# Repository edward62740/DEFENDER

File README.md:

# DEFENDER

This is a 2.4GHz Wi-Fi scanner for estimating channel usage and detect deauthentication attacks. The collected data is sent to a database to be analyzed and provide notifications.

## Design Objectives

* Provide notifications on deauthentication attacks (including which channel(s) they are on).
* Allow for measurement of 2.4GHz Wi-Fi channel packets per second to estimate channel noise. Since Wi-Fi is the biggest "polluter" of 2.4GHz in residential environments, this data can be used to steer other linked systems clear of noisy channel frequencies.

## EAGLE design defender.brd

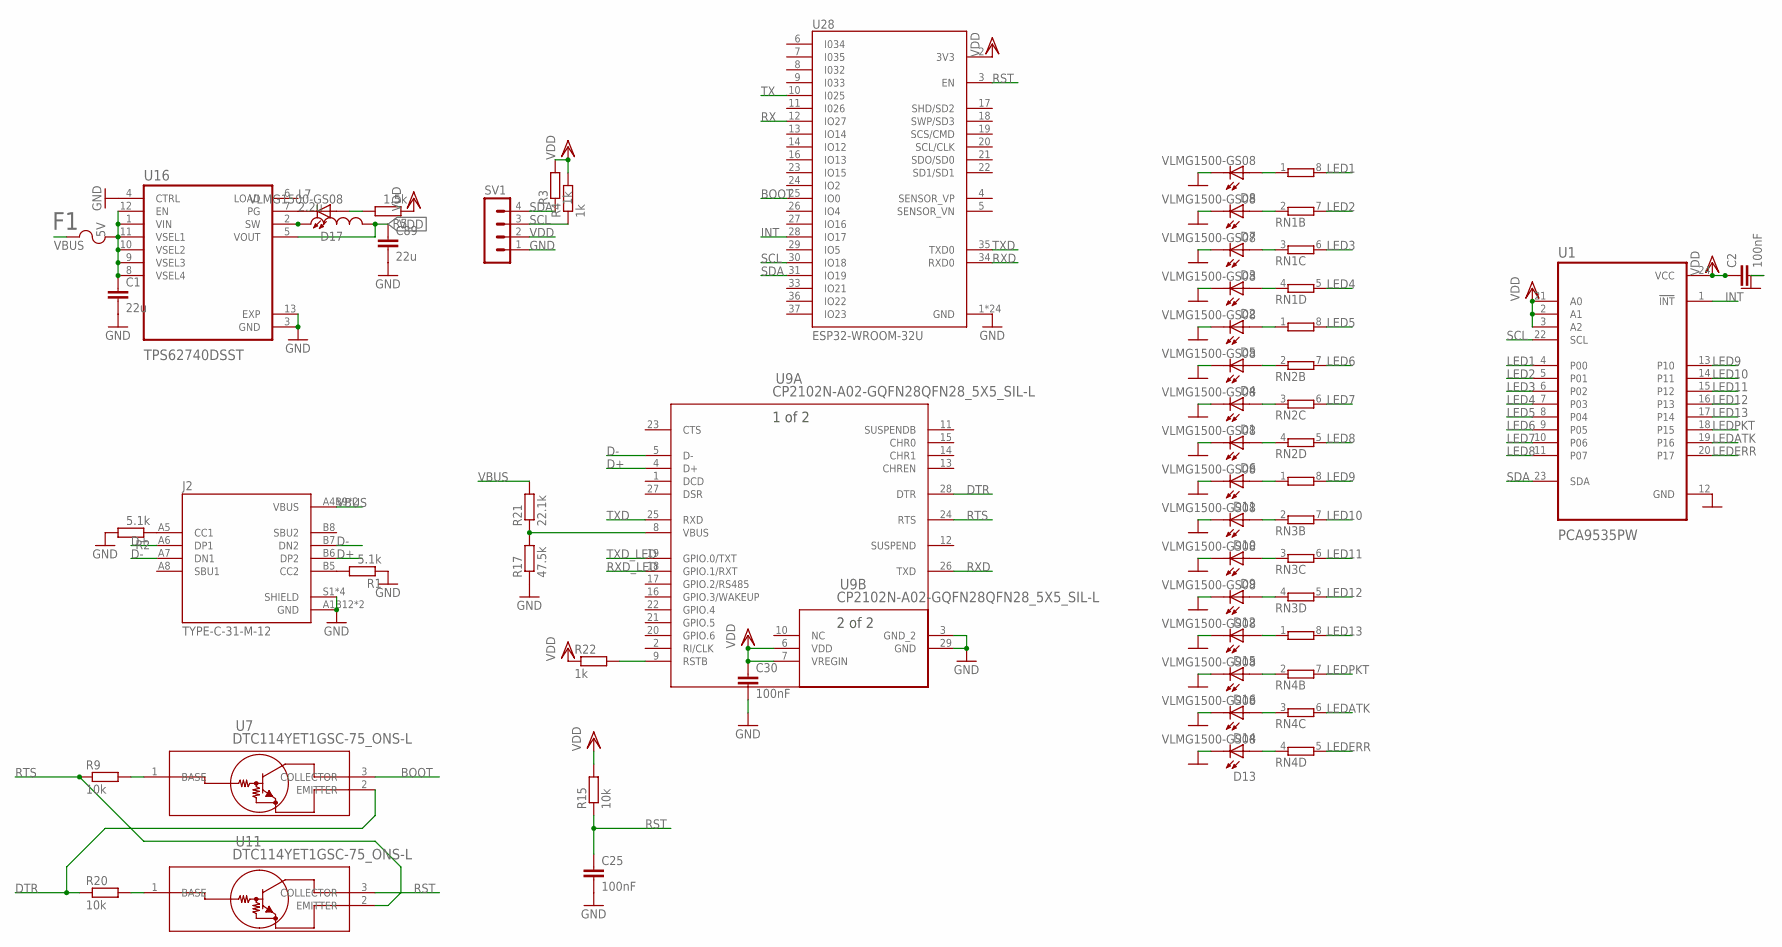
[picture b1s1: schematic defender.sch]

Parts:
C1, C89: 22u; C0603R
C2, C25, C30: 100nF; C0402
D1, D2, D3, D4, D5, D6, D7, D8, D9, D10, D11, D12, D13, D14, D15, D16, D17: VLMG1500-GS08; LEDC1005X35N
F1: 1210L050YR1210LSERIES_LTF-L; 1210LSERIES_LTF-L
J2: TYPE-C-31-M-12; HRO_TYPE-C-31-M-12
L7: 2.2u; INDC3225X120N
R1, R2: 5.1k; R0402
R3, R4, R22: 1k; R0402
R5: 1.5k; R0402
R9, R15, R20: 10k; R0402
R17: 47.5k; R0402
R21: 22.1k; R0402
RN1, RN2, RN3, RN4: 4R-N0402ARV341; 4X0402ARV341
SV1: MA04-1
U1: PCA9535PW; SOP65P640X120-24N
U7, U11: DTC114YET1GSC-75_ONS-L; SC-75_ONS-L
U9: CP2102N-A02-GQFN28QFN28_5X5_SIL-L; QFN28_5X5_SIL-L
U16: TPS62740DSST; VREG_LM27762DSSR
U28: ESP32-WROOM-32U; XCVR_ESP32-WROOM-32U

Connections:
5V: C1.1, F1.2, U16.1 (VIN), U16.8 (VSEL4), U16.9 (VSEL3), U16.10 (VSEL2), U16.11 (VSEL1), U16.12 (EN)
BOOT: U7.3 (COLLECTOR), U28.25 (IO0)
D+: J2.A6 (DP1), J2.B6 (DP2), U9.4 (D+)
D-: J2.A7 (DN1), J2.B7 (DN2), U9.5 (D-)
DTR: R20.1, U7.2 (EMITTER), U9.28 (DTR)
GND: C1.2, C2.2, C25.2, C30.2, C89.2, D1.2, D2.2, D3.2, D4.2, D5.2, D6.2, D7.2, D8.2, D9.2, D10.2, D11.2, D12.2, D13.2, D14.2, D15.2, D16.2, J2.A1B12 (GND), J2.B1A12 (GND), J2.S1 (SHIELD), J2.S2 (SHIELD), J2.S3 (SHIELD), J2.S4 (SHIELD), R1.1, R2.2, R17.1, SV1.1, U1.12 (GND), U9.3 (GND_2), U9.29 (GND), U16.3 (GND), U16.4 (CTRL), U16.13 (EXP), U28.1 (GND), U28.15 (GND), U28.38 (GND), U28.G.1 (GND), U28.G.2 (GND), U28.G.4 (GND), U28.G.5 (GND), U28.G.6 (GND), U28.G.7 (GND), U28.G.8 (GND), U28.G.9 (GND), U28.G.10 (GND), U28.G.11 (GND), U28.G.12 (GND), U28.G.13 (GND), U28.G.14 (GND), U28.G.15 (GND), U28.G.16 (GND), U28.G.17 (GND), U28.G.18 (GND), U28.G.19 (GND), U28.G.20 (GND), U28.G.21 (GND), U28.G.22 (GND)
INT: U1.1 (!INT), U28.28 (IO17)
LED1: RN1.8 (2), U1.4 (P00)
LED2: RN1.7 (2), U1.5 (P01)
LED3: RN1.6 (2), U1.6 (P02)
LED4: RN1.5 (2), U1.7 (P03)
LED5: RN2.8 (2), U1.8 (P04)
LED6: RN2.7 (2), U1.9 (P05)
LED7: RN2.6 (2), U1.10 (P06)
LED8: RN2.5 (2), U1.11 (P07)
LED9: RN3.8 (2), U1.13 (P10)
LED10: RN3.7 (2), U1.14 (P11)
LED11: RN3.6 (2), U1.15 (P12)
LED12: RN3.5 (2), U1.16 (P13)
LED13: RN4.8 (2), U1.17 (P14)
LEDATK: RN4.6 (2), U1.19 (P16)
LEDERR: RN4.5 (2), U1.20 (P17)
LEDPKT: RN4.7 (2), U1.18 (P15)
unnamed: J2.B5 (CC2), R1.2
unnamed: J2.A5 (CC1), R2.1
unnamed: D1.1, RN2.3 (1)
unnamed: D4.1, RN2.2 (1)
unnamed: D5.1, RN2.1
unnamed: D6.1, RN2.4 (1)
unnamed: D9.1, RN3.3 (1)
unnamed: D10.1, RN3.2 (1)
unnamed: D11.1, RN3.1
unnamed: D12.1, RN3.4 (1)
unnamed: D13.1, RN4.4 (1)
unnamed: D14.1, RN4.3 (1)
unnamed: D15.1, RN4.1
unnamed: D16.1, RN4.2 (1)
unnamed: D17.1, R5.2
unnamed: D17.2, U16.7 (PG)
unnamed: D3.1, RN1.3 (1)
unnamed: D7.1, RN1.2 (1)
unnamed: D8.1, RN1.1
unnamed: R17.2, R21.1, U9.8 (VBUS)
unnamed: D2.1, RN1.4 (1)
unnamed: R20.2, U11.1 (BASE)
unnamed: R9.2, U7.1 (BASE)
unnamed: R22.2, U9.9 (RSTB)
unnamed: L7.1, U16.2 (SW)
RST: C25.1, R15.1, U11.3 (COLLECTOR), U28.3 (EN)
RTS: R9.1, U9.24 (RTS), U11.2 (EMITTER)
RX: U28.12 (IO27)
RXD: U9.26 (TXD), U28.34 (RXD0)
RXD_LED: U9.18 (GPIO.1/RXT)
SCL: R4.1, SV1.3, U1.22 (SCL), U28.30 (IO18)
SDA: R3.1, SV1.4, U1.23 (SDA), U28.31 (IO19)
TX: U28.10 (I025)
TXD: U9.25 (RXD), U28.35 (TXD0)
TXD_LED: U9.19 (GPIO.0/TXT)
VBUS: F1.1, J2.A4B9 (VBUS), J2.B4A9 (VBUS), R21.2
VDD: C2.1, C30.1, C89.1, L7.2, R3.2, R4.2, R5.1, R15.2, R22.1, SV1.2, U1.2 (A1), U1.3 (A2), U1.21 (A0), U1.24 (VCC), U9.6 (VDD), U9.7 (VREGIN), U16.5 (VOUT), U28.2 (3V3)

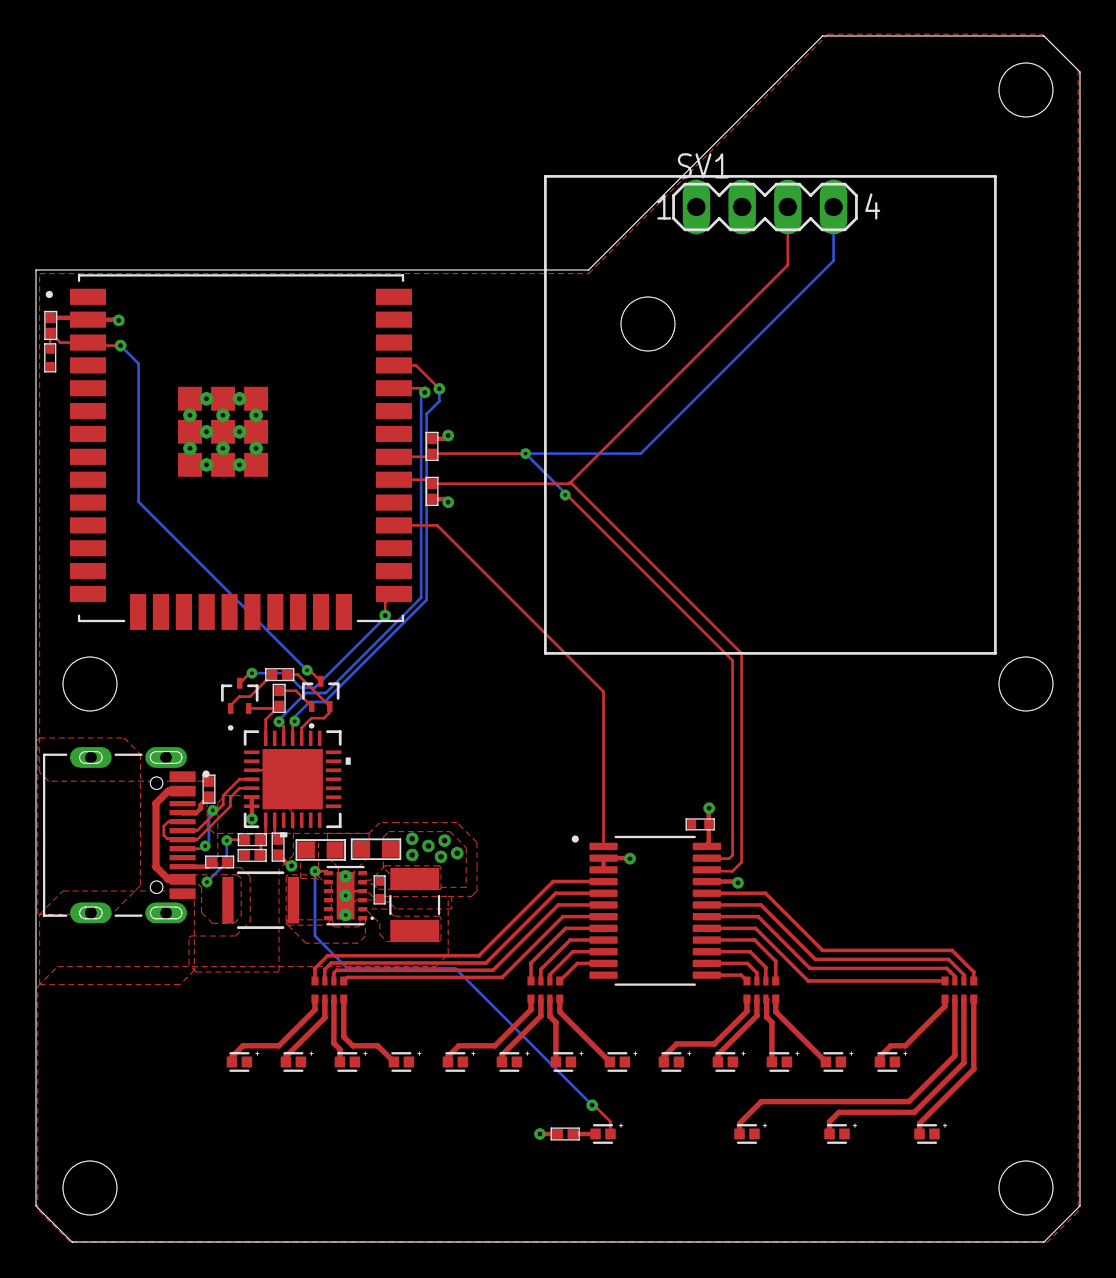
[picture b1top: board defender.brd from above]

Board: 4 copper layers, 58.0 x 67.0 mm, 47 parts (0 on the bottom side), 56 nets.

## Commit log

2022-01-30 Added PCB files
2022-01-30 Added stl

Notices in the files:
parts and their libraries:
COPYRIGHT: Copyright (C) 2018 Accelerated Designs. All rights reserved
